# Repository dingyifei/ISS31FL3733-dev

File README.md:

# ISS31FL3733-dev
a 3733 dev board that might just work

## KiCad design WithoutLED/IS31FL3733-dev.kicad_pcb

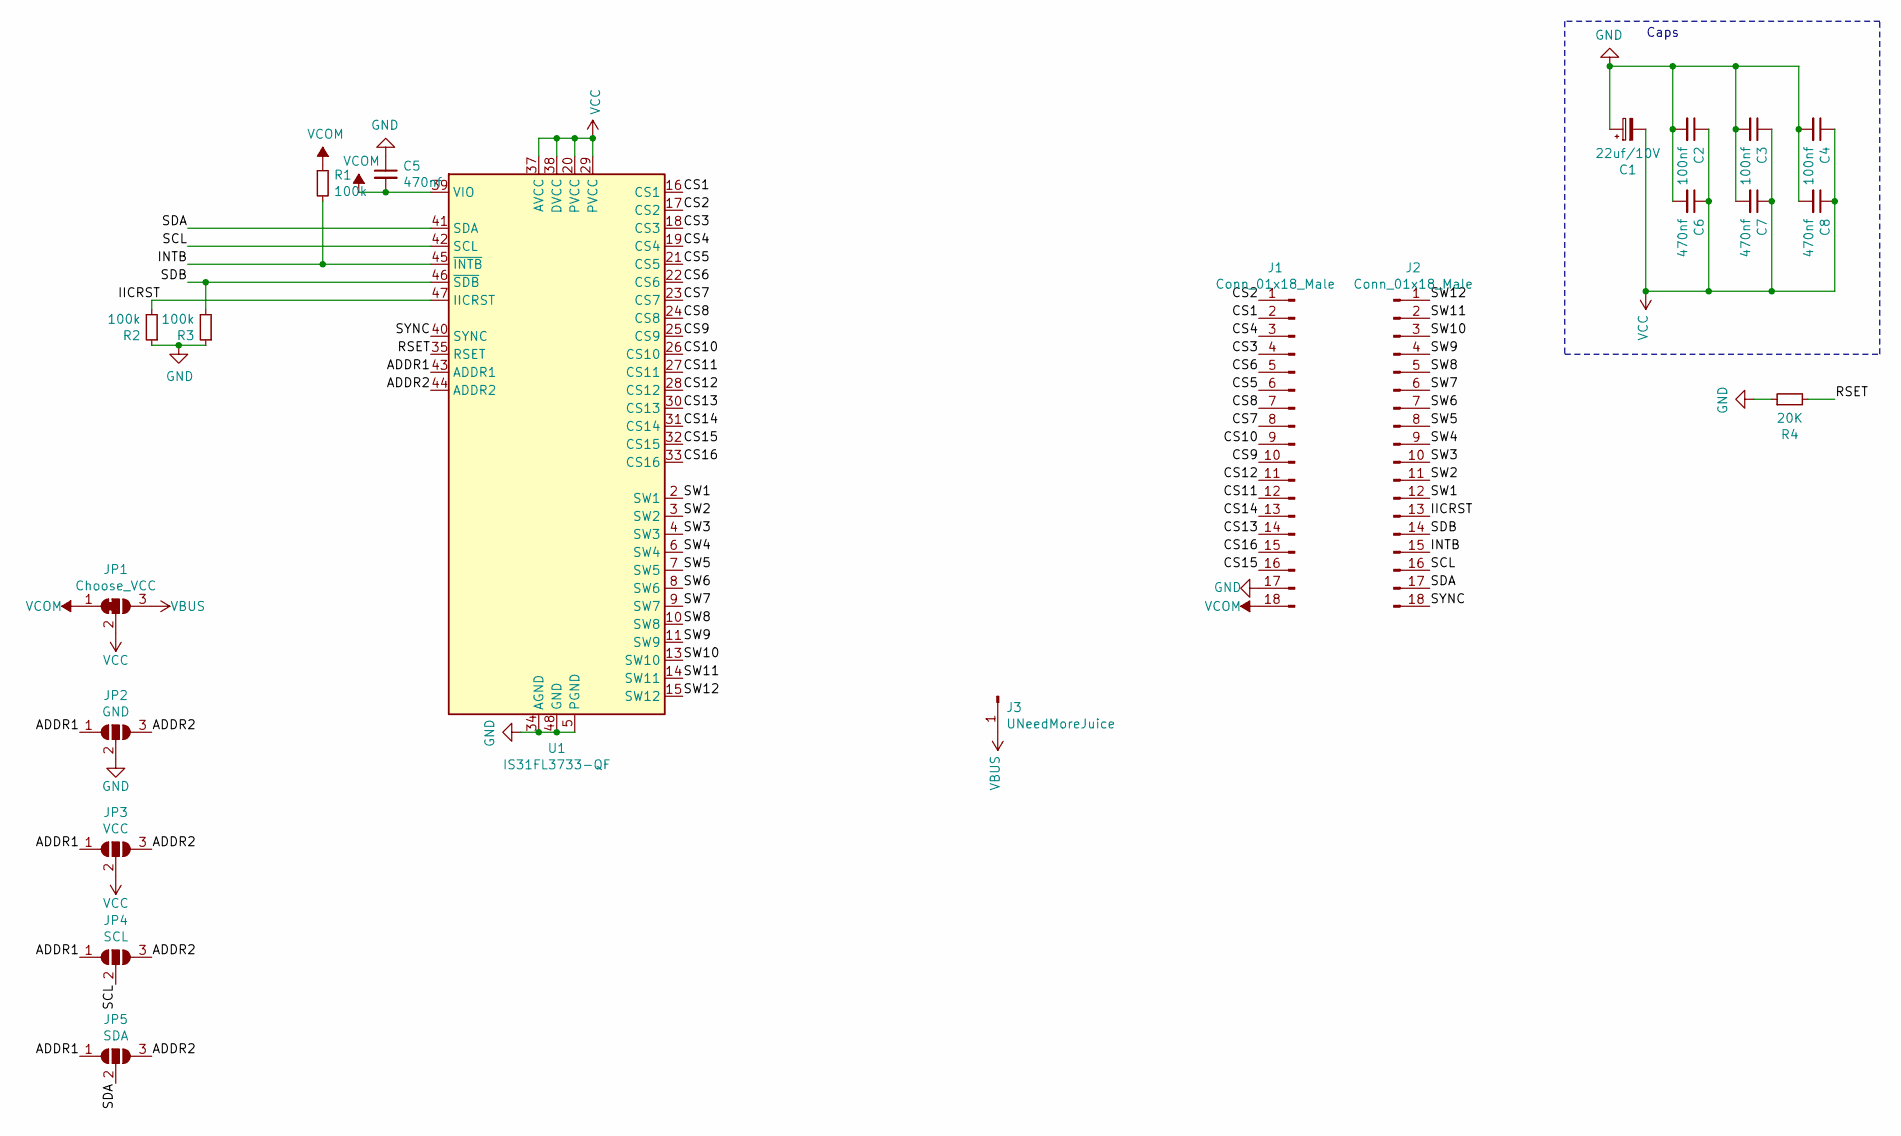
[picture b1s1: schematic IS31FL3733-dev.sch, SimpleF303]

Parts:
C1: 22uf/10V; CP_EIA-3216-18_Kemet-A; LCSC C11366
C2, C3, C4: 100nf; C_0603_1608Metric; LCSC C80516
C5, C6, C7, C8: 470nf; C_0603_1608Metric; LCSC C170149
J1, J2: Conn_01x18_Male; PinHeader_2x09_P2.00mm_Vertical
J3: UNeedMoreJuice; PinHeader_1x01_P2.00mm_Vertical
JP1: Choose_VCC; SolderJumper-3_P1.3mm_Open_RoundedPad1.0x1.5mm
JP2: GND; SolderJumper-3_P1.3mm_Open_RoundedPad1.0x1.5mm
JP3: VCC; SolderJumper-3_P1.3mm_Open_RoundedPad1.0x1.5mm
JP4: SCL; SolderJumper-3_P1.3mm_Open_RoundedPad1.0x1.5mm
JP5: SDA; SolderJumper-3_P1.3mm_Open_RoundedPad1.0x1.5mm
R1, R2, R3: 100k; R_0603_1608Metric; LCSC C100703
R4: 20K; R_0603_1608Metric; LCSC C100865
U1: IS31FL3733-QF; QFN-48-1EP_6x6mm_P0.4mm_EP4.2x4.2mm_ThermalVias

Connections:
/ADDR1: JP2.1 (A), JP3.1 (A), JP4.1 (A), JP5.1 (A), U1.43 (ADDR1)
/ADDR2: JP2.3 (B), JP3.3 (B), JP4.3 (B), JP5.3 (B), U1.44 (ADDR2)
/CS1: J1.2, U1.16 (CS1)
/CS2: J1.1, U1.17 (CS2)
/CS3: J1.4, U1.18 (CS3)
/CS4: J1.3, U1.19 (CS4)
/CS5: J1.6, U1.21 (CS5)
/CS6: J1.5, U1.22 (CS6)
/CS7: J1.8, U1.23 (CS7)
/CS8: J1.7, U1.24 (CS8)
/CS9: J1.10, U1.25 (CS9)
/CS10: J1.9, U1.26 (CS10)
/CS11: J1.12, U1.27 (CS11)
/CS12: J1.11, U1.28 (CS12)
/CS13: J1.14, U1.30 (CS13)
/CS14: J1.13, U1.31 (CS14)
/CS15: J1.16, U1.32 (CS15)
/CS16: J1.15, U1.33 (CS16)
/IICRST: J2.13, R2.2, U1.47 (IICRST)
/INTB: J2.15, R1.2, U1.45 (~INTB)
/RSET: R4.2, U1.35 (RSET)
/SCL: J2.16, JP4.2 (C), U1.42 (SCL)
/SDA: J2.17, JP5.2 (C), U1.41 (SDA)
/SDB: J2.14, R3.2, U1.46 (~SDB)
/SW1: J2.12, U1.2 (SW1)
/SW2: J2.11, U1.3 (SW2)
/SW3: J2.10, U1.4 (SW3)
/SW4: J2.9, U1.6 (SW4)
/SW5: J2.8, U1.7 (SW5)
/SW6: J2.7, U1.8 (SW6)
/SW7: J2.6, U1.9 (SW7)
/SW8: J2.5, U1.10 (SW8)
/SW9: J2.4, U1.11 (SW9)
/SW10: J2.3, U1.13 (SW10)
/SW11: J2.2, U1.14 (SW11)
/SW12: J2.1, U1.15 (SW12)
/SYNC: J2.18, U1.40 (SYNC)
GND: C1.1, C2.2, C3.2, C4.2, C5.1, C6.2, C7.2, C8.2, J1.17, JP2.2 (C), R2.1, R3.1, R4.1, U1.5 (PGND), U1.12 (PGND), U1.34 (AGND), U1.48 (GND), U1.49 (GND)
VBUS: J3.1, JP1.3 (B)
VCC: C1.2, C2.1, C3.1, C4.1, C6.1, C7.1, C8.1, JP1.2 (C), JP3.2 (C), U1.20 (PVCC), U1.29 (PVCC), U1.37 (AVCC), U1.38 (DVCC)
VCOM: C5.2, J1.18, JP1.1 (A), R1.1, U1.39 (VIO)

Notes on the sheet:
Caps

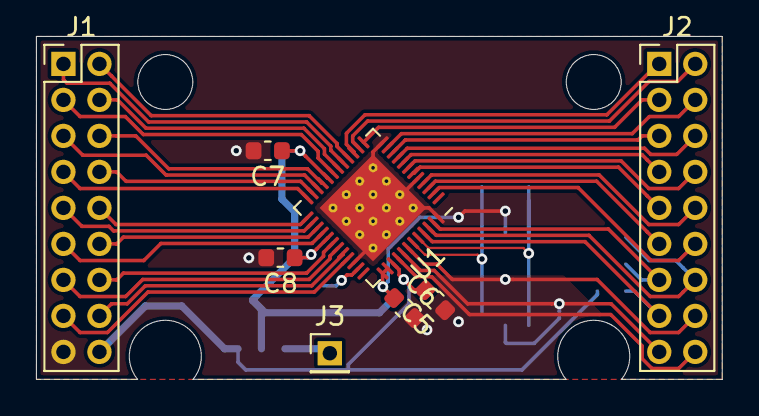
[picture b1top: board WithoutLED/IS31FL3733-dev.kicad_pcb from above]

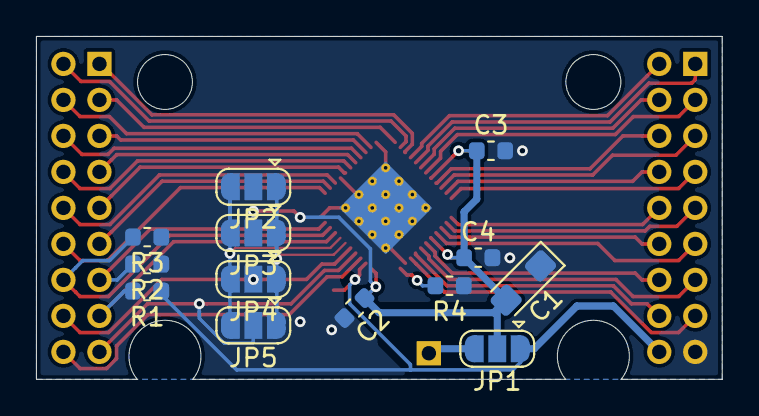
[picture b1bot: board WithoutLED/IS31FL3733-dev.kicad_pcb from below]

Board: 2 copper layers, 38.1 x 19.1 mm, 21 parts (13 on the bottom side), 41 nets.

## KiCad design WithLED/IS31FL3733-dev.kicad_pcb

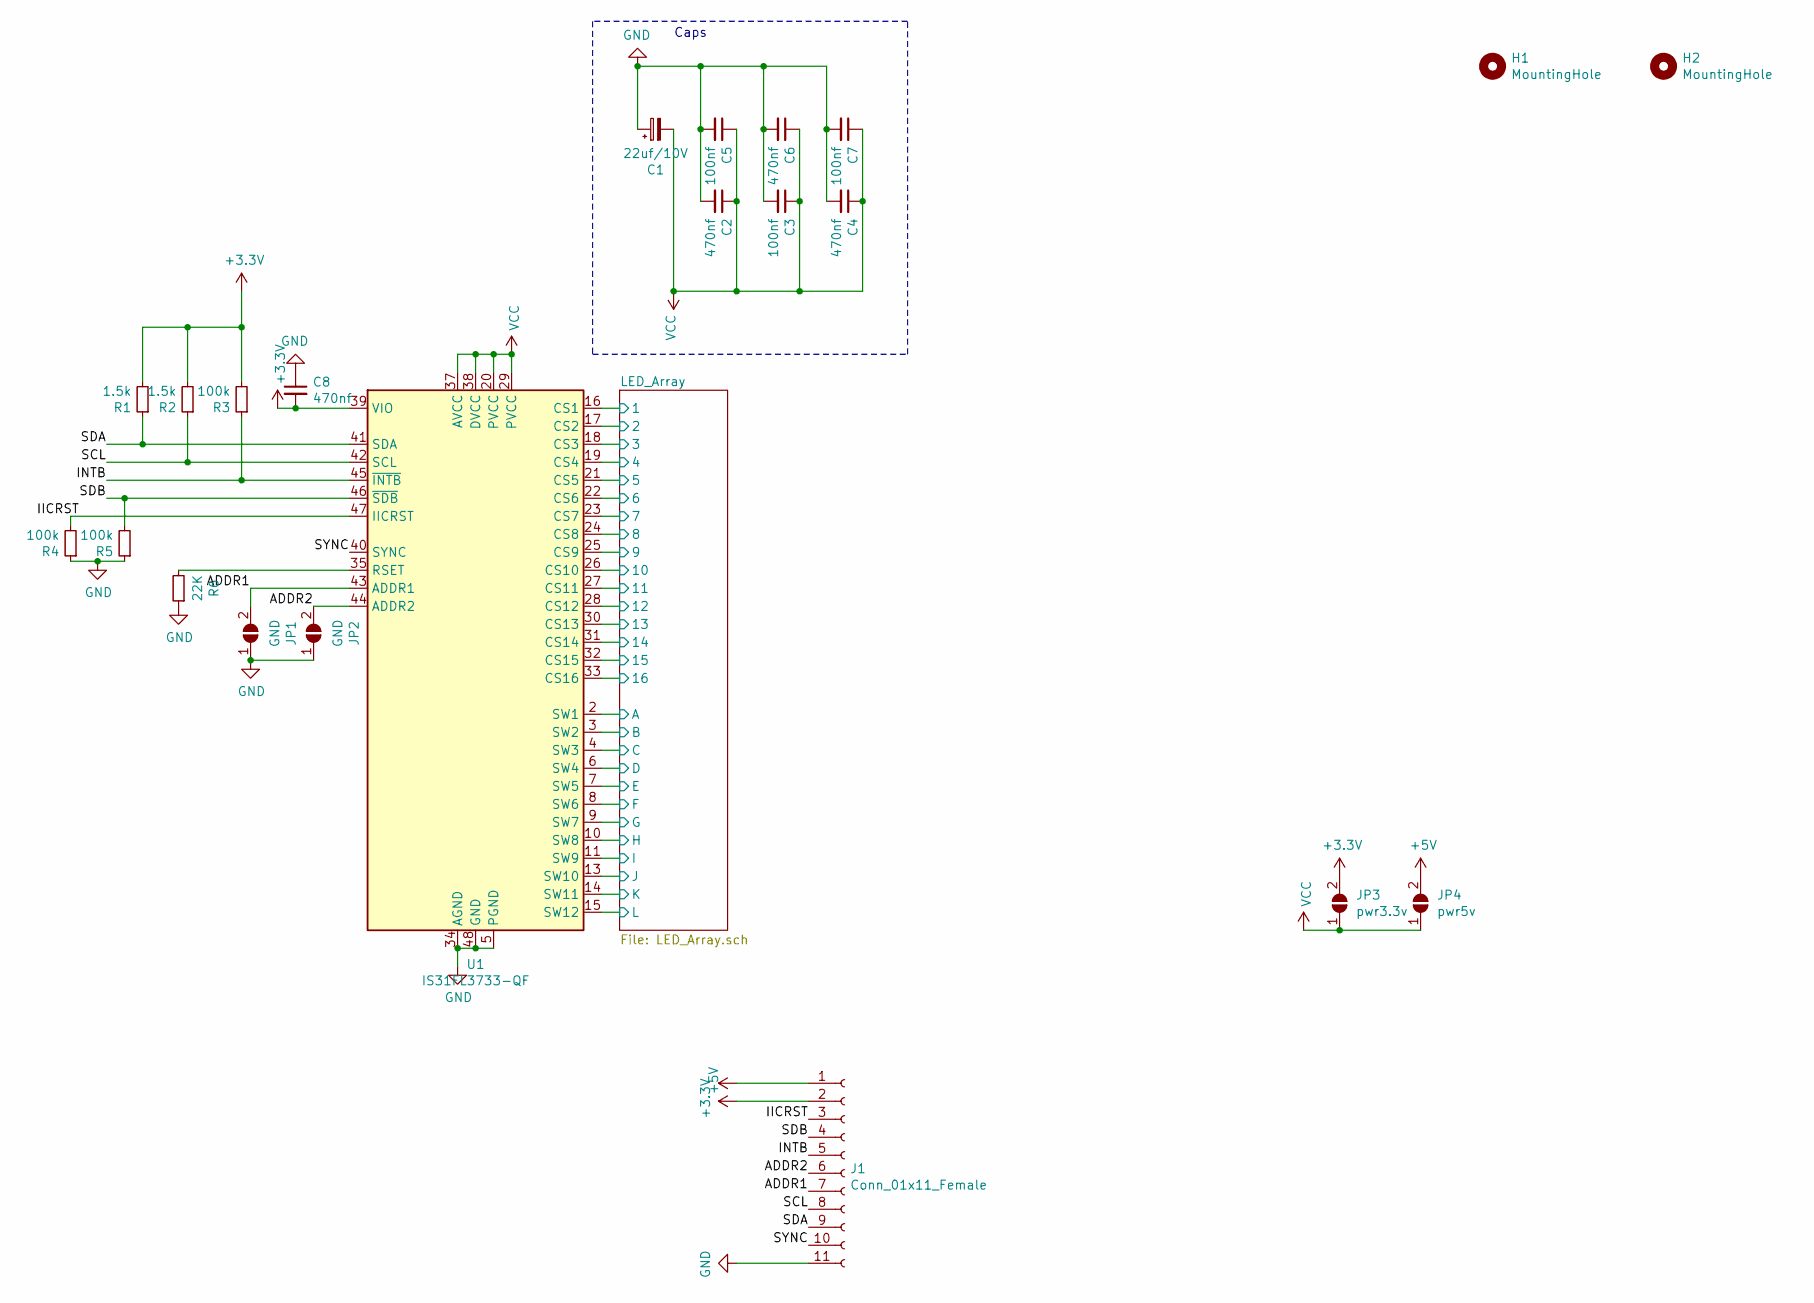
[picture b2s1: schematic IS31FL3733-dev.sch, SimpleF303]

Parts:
C1: 22uf/10V; CP_EIA-3216-18_Kemet-A; LCSC C11366
C2, C4, C6, C8: 470nf; C_0603_1608Metric; LCSC C170149
C3, C5, C7: 100nf; C_0603_1608Metric; LCSC C80516
H1, H2: MountingHole; MountingHole_2.1mm; LCSC C2337
J1: Conn_01x11_Female; PinSocket_1x11_P2.54mm_Vertical; LCSC C2337
JP1, JP2: GND; SolderJumper-2_P1.3mm_Open_TrianglePad1.0x1.5mm
JP3: pwr3.3v; SolderJumper-2_P1.3mm_Open_TrianglePad1.0x1.5mm
JP4: pwr5v; SolderJumper-2_P1.3mm_Open_TrianglePad1.0x1.5mm
R1, R2: 1.5k; R_0603_1608Metric; LCSC C103303
R3, R4, R5: 100k; R_0603_1608Metric; LCSC C100703
R6: 22K; R_0603_1608Metric; LCSC C100865
U1: IS31FL3733-QF; QFN-48-1EP_6x6mm_P0.4mm_EP4.2x4.2mm_ThermalVias

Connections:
+3V3: C8.2, J1.2, JP3.2 (B), R1.2, R2.2, R3.2, U1.39 (VIO)
+5V: J1.1, JP4.2 (B)
/ADDR1: J1.7, JP1.2 (B), U1.43 (ADDR1)
/ADDR2: J1.6, JP2.2 (B), U1.44 (ADDR2)
/IICRST: J1.3, R4.2, U1.47 (IICRST)
/INTB: J1.5, R3.1, U1.45 (~INTB)
/LED_Array/1: U1.16 (CS1); also elsewhere on the board
/LED_Array/2: U1.17 (CS2); also elsewhere on the board
/LED_Array/3: U1.18 (CS3); also elsewhere on the board
/LED_Array/4: U1.19 (CS4); also elsewhere on the board
/LED_Array/5: U1.21 (CS5); also elsewhere on the board
/LED_Array/6: U1.22 (CS6); also elsewhere on the board
/LED_Array/7: U1.23 (CS7); also elsewhere on the board
/LED_Array/8: U1.24 (CS8); also elsewhere on the board
/LED_Array/9: U1.25 (CS9); also elsewhere on the board
/LED_Array/10: U1.26 (CS10); also elsewhere on the board
/LED_Array/11: U1.27 (CS11); also elsewhere on the board
/LED_Array/12: U1.28 (CS12); also elsewhere on the board
/LED_Array/13: U1.30 (CS13); also elsewhere on the board
/LED_Array/14: U1.31 (CS14); also elsewhere on the board
/LED_Array/15: U1.32 (CS15); also elsewhere on the board
/LED_Array/16: U1.33 (CS16); also elsewhere on the board
/LED_Array/A: U1.2 (SW1); also elsewhere on the board
/LED_Array/B: U1.3 (SW2); also elsewhere on the board
/LED_Array/C: U1.4 (SW3); also elsewhere on the board
/LED_Array/D: U1.6 (SW4); also elsewhere on the board
/LED_Array/E: U1.7 (SW5); also elsewhere on the board
/LED_Array/F: U1.8 (SW6); also elsewhere on the board
/LED_Array/G: U1.9 (SW7); also elsewhere on the board
/LED_Array/H: U1.10 (SW8); also elsewhere on the board
/LED_Array/I: U1.11 (SW9); also elsewhere on the board
/LED_Array/J: U1.13 (SW10); also elsewhere on the board
/LED_Array/K: U1.14 (SW11); also elsewhere on the board
/LED_Array/L: U1.15 (SW12); also elsewhere on the board
/SCL: J1.8, R2.1, U1.42 (SCL)
/SDA: J1.9, R1.1, U1.41 (SDA)
/SDB: J1.4, R5.2, U1.46 (~SDB)
/SYNC: J1.10, U1.40 (SYNC)
GND: C1.1, C2.2, C3.2, C4.2, C5.2, C6.2, C7.2, C8.1, J1.11, JP1.1 (A), JP2.1 (A), R4.1, R5.1, R6.1, U1.5 (PGND), U1.12 (PGND), U1.34 (AGND), U1.48 (GND), U1.49 (GND)
unnamed: R6.2, U1.35 (RSET)
VCC: C1.2, C2.1, C3.1, C4.1, C5.1, C6.1, C7.1, JP3.1 (A), JP4.1 (A), U1.20 (PVCC), U1.29 (PVCC), U1.37 (AVCC), U1.38 (DVCC)

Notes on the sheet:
Caps

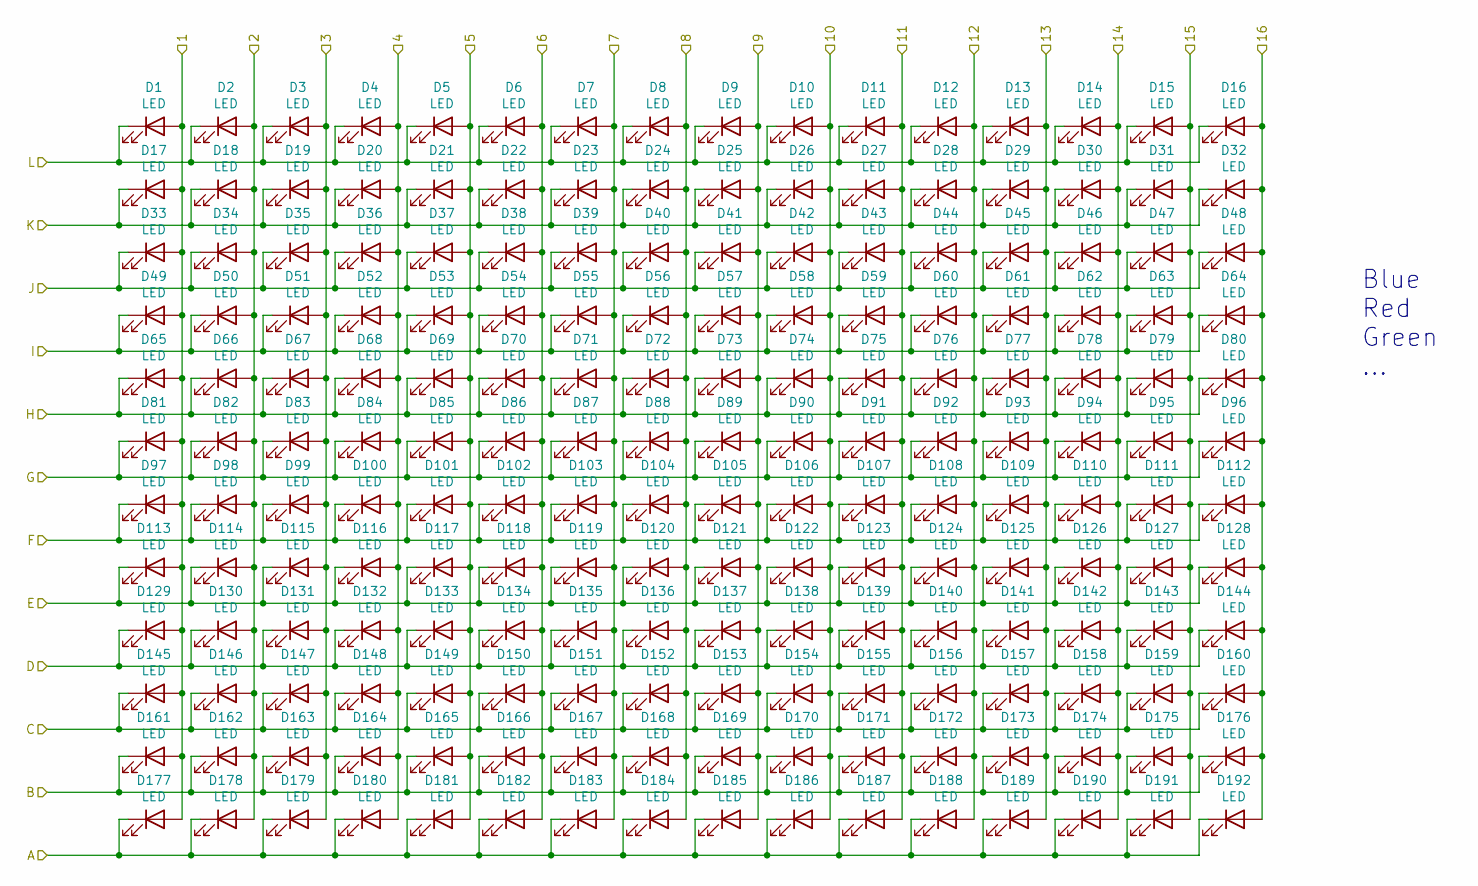
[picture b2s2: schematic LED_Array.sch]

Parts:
D1, D2, D3, D4, D5, D6, D7, D8, D9, D10, D11, D12, D13, D14, D15, D16, D17, D18, D19, D20, D21, D22, D23, D24, D25, D26, D27, D28, D29, D30, D31, D32, D33, D34, D35, D36, D37, D38, D39, D40, D41, D42, D43, D44, D45, D46, D47, D48, D49, D50, D51, D52, D53, D54, D55, D56, D57, D58, D59, D60, D61, D62, D63, D64, D65, D66, D67, D68, D69, D70, D71, D72, D73, D74, D75, D76, D77, D78, D79, D80, D81, D82, D83, D84, D85, D86, D87, D88, D89, D90, D91, D92, D93, D94, D95, D96, D97, D98, D99, D100, D101, D102, D103, D104, D105, D106, D107, D108, D109, D110, D111, D112, D113, D114, D115, D116, D117, D118, D119, D120, D121, D122, D123, D124, D125, D126, D127, D128, D129, D130, D131, D132, D133, D134, D135, D136, D137, D138, D139, D140, D141, D142, D143, D144, D145, D146, D147, D148, D149, D150, D151, D152, D153, D154, D155, D156, D157, D158, D159, D160, D161, D162, D163, D164, D165, D166, D167, D168, D169, D170, D171, D172, D173, D174, D175, D176, D177, D178, D179, D180, D181, D182, D183, D184, D185, D186, D187, D188, D189, D190, D191, D192: LED; LED_0603_1608Metric_HideText

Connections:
/LED_Array/1: D1.2 (A), D17.2 (A), D33.2 (A), D49.2 (A), D65.2 (A), D81.2 (A), D97.2 (A), D113.2 (A), D129.2 (A), D145.2 (A), D161.2 (A), D177.2 (A); also elsewhere on the board
/LED_Array/2: D2.2 (A), D18.2 (A), D34.2 (A), D50.2 (A), D66.2 (A), D82.2 (A), D98.2 (A), D114.2 (A), D130.2 (A), D146.2 (A), D162.2 (A), D178.2 (A); also elsewhere on the board
/LED_Array/3: D3.2 (A), D19.2 (A), D35.2 (A), D51.2 (A), D67.2 (A), D83.2 (A), D99.2 (A), D115.2 (A), D131.2 (A), D147.2 (A), D163.2 (A), D179.2 (A); also elsewhere on the board
/LED_Array/4: D4.2 (A), D20.2 (A), D36.2 (A), D52.2 (A), D68.2 (A), D84.2 (A), D100.2 (A), D116.2 (A), D132.2 (A), D148.2 (A), D164.2 (A), D180.2 (A); also elsewhere on the board
/LED_Array/5: D5.2 (A), D21.2 (A), D37.2 (A), D53.2 (A), D69.2 (A), D85.2 (A), D101.2 (A), D117.2 (A), D133.2 (A), D149.2 (A), D165.2 (A), D181.2 (A); also elsewhere on the board
/LED_Array/6: D6.2 (A), D22.2 (A), D38.2 (A), D54.2 (A), D70.2 (A), D86.2 (A), D102.2 (A), D118.2 (A), D134.2 (A), D150.2 (A), D166.2 (A), D182.2 (A); also elsewhere on the board
/LED_Array/7: D7.2 (A), D23.2 (A), D39.2 (A), D55.2 (A), D71.2 (A), D87.2 (A), D103.2 (A), D119.2 (A), D135.2 (A), D151.2 (A), D167.2 (A), D183.2 (A); also elsewhere on the board
/LED_Array/8: D8.2 (A), D24.2 (A), D40.2 (A), D56.2 (A), D72.2 (A), D88.2 (A), D104.2 (A), D120.2 (A), D136.2 (A), D152.2 (A), D168.2 (A), D184.2 (A); also elsewhere on the board
/LED_Array/9: D9.2 (A), D25.2 (A), D41.2 (A), D57.2 (A), D73.2 (A), D89.2 (A), D105.2 (A), D121.2 (A), D137.2 (A), D153.2 (A), D169.2 (A), D185.2 (A); also elsewhere on the board
/LED_Array/10: D10.2 (A), D26.2 (A), D42.2 (A), D58.2 (A), D74.2 (A), D90.2 (A), D106.2 (A), D122.2 (A), D138.2 (A), D154.2 (A), D170.2 (A), D186.2 (A); also elsewhere on the board
/LED_Array/11: D11.2 (A), D27.2 (A), D43.2 (A), D59.2 (A), D75.2 (A), D91.2 (A), D107.2 (A), D123.2 (A), D139.2 (A), D155.2 (A), D171.2 (A), D187.2 (A); also elsewhere on the board
/LED_Array/12: D12.2 (A), D28.2 (A), D44.2 (A), D60.2 (A), D76.2 (A), D92.2 (A), D108.2 (A), D124.2 (A), D140.2 (A), D156.2 (A), D172.2 (A), D188.2 (A); also elsewhere on the board
/LED_Array/13: D13.2 (A), D29.2 (A), D45.2 (A), D61.2 (A), D77.2 (A), D93.2 (A), D109.2 (A), D125.2 (A), D141.2 (A), D157.2 (A), D173.2 (A), D189.2 (A); also elsewhere on the board
/LED_Array/14: D14.2 (A), D30.2 (A), D46.2 (A), D62.2 (A), D78.2 (A), D94.2 (A), D110.2 (A), D126.2 (A), D142.2 (A), D158.2 (A), D174.2 (A), D190.2 (A); also elsewhere on the board
/LED_Array/15: D15.2 (A), D31.2 (A), D47.2 (A), D63.2 (A), D79.2 (A), D95.2 (A), D111.2 (A), D127.2 (A), D143.2 (A), D159.2 (A), D175.2 (A), D191.2 (A); also elsewhere on the board
/LED_Array/16: D16.2 (A), D32.2 (A), D48.2 (A), D64.2 (A), D80.2 (A), D96.2 (A), D112.2 (A), D128.2 (A), D144.2 (A), D160.2 (A), D176.2 (A), D192.2 (A); also elsewhere on the board
/LED_Array/A: D177.1 (K), D178.1 (K), D179.1 (K), D180.1 (K), D181.1 (K), D182.1 (K), D183.1 (K), D184.1 (K), D185.1 (K), D186.1 (K), D187.1 (K), D188.1 (K), D189.1 (K), D190.1 (K), D191.1 (K), D192.1 (K); also elsewhere on the board
/LED_Array/B: D161.1 (K), D162.1 (K), D163.1 (K), D164.1 (K), D165.1 (K), D166.1 (K), D167.1 (K), D168.1 (K), D169.1 (K), D170.1 (K), D171.1 (K), D172.1 (K), D173.1 (K), D174.1 (K), D175.1 (K), D176.1 (K); also elsewhere on the board
/LED_Array/C: D145.1 (K), D146.1 (K), D147.1 (K), D148.1 (K), D149.1 (K), D150.1 (K), D151.1 (K), D152.1 (K), D153.1 (K), D154.1 (K), D155.1 (K), D156.1 (K), D157.1 (K), D158.1 (K), D159.1 (K), D160.1 (K); also elsewhere on the board
/LED_Array/D: D129.1 (K), D130.1 (K), D131.1 (K), D132.1 (K), D133.1 (K), D134.1 (K), D135.1 (K), D136.1 (K), D137.1 (K), D138.1 (K), D139.1 (K), D140.1 (K), D141.1 (K), D142.1 (K), D143.1 (K), D144.1 (K); also elsewhere on the board
/LED_Array/E: D113.1 (K), D114.1 (K), D115.1 (K), D116.1 (K), D117.1 (K), D118.1 (K), D119.1 (K), D120.1 (K), D121.1 (K), D122.1 (K), D123.1 (K), D124.1 (K), D125.1 (K), D126.1 (K), D127.1 (K), D128.1 (K); also elsewhere on the board
/LED_Array/F: D97.1 (K), D98.1 (K), D99.1 (K), D100.1 (K), D101.1 (K), D102.1 (K), D103.1 (K), D104.1 (K), D105.1 (K), D106.1 (K), D107.1 (K), D108.1 (K), D109.1 (K), D110.1 (K), D111.1 (K), D112.1 (K); also elsewhere on the board
/LED_Array/G: D81.1 (K), D82.1 (K), D83.1 (K), D84.1 (K), D85.1 (K), D86.1 (K), D87.1 (K), D88.1 (K), D89.1 (K), D90.1 (K), D91.1 (K), D92.1 (K), D93.1 (K), D94.1 (K), D95.1 (K), D96.1 (K); also elsewhere on the board
/LED_Array/H: D65.1 (K), D66.1 (K), D67.1 (K), D68.1 (K), D69.1 (K), D70.1 (K), D71.1 (K), D72.1 (K), D73.1 (K), D74.1 (K), D75.1 (K), D76.1 (K), D77.1 (K), D78.1 (K), D79.1 (K), D80.1 (K); also elsewhere on the board
/LED_Array/I: D49.1 (K), D50.1 (K), D51.1 (K), D52.1 (K), D53.1 (K), D54.1 (K), D55.1 (K), D56.1 (K), D57.1 (K), D58.1 (K), D59.1 (K), D60.1 (K), D61.1 (K), D62.1 (K), D63.1 (K), D64.1 (K); also elsewhere on the board
/LED_Array/J: D33.1 (K), D34.1 (K), D35.1 (K), D36.1 (K), D37.1 (K), D38.1 (K), D39.1 (K), D40.1 (K), D41.1 (K), D42.1 (K), D43.1 (K), D44.1 (K), D45.1 (K), D46.1 (K), D47.1 (K), D48.1 (K); also elsewhere on the board
/LED_Array/K: D17.1 (K), D18.1 (K), D19.1 (K), D20.1 (K), D21.1 (K), D22.1 (K), D23.1 (K), D24.1 (K), D25.1 (K), D26.1 (K), D27.1 (K), D28.1 (K), D29.1 (K), D30.1 (K), D31.1 (K), D32.1 (K); also elsewhere on the board
/LED_Array/L: D1.1 (K), D2.1 (K), D3.1 (K), D4.1 (K), D5.1 (K), D6.1 (K), D7.1 (K), D8.1 (K), D9.1 (K), D10.1 (K), D11.1 (K), D12.1 (K), D13.1 (K), D14.1 (K), D15.1 (K), D16.1 (K); also elsewhere on the board

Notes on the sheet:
Blue Red Green ...

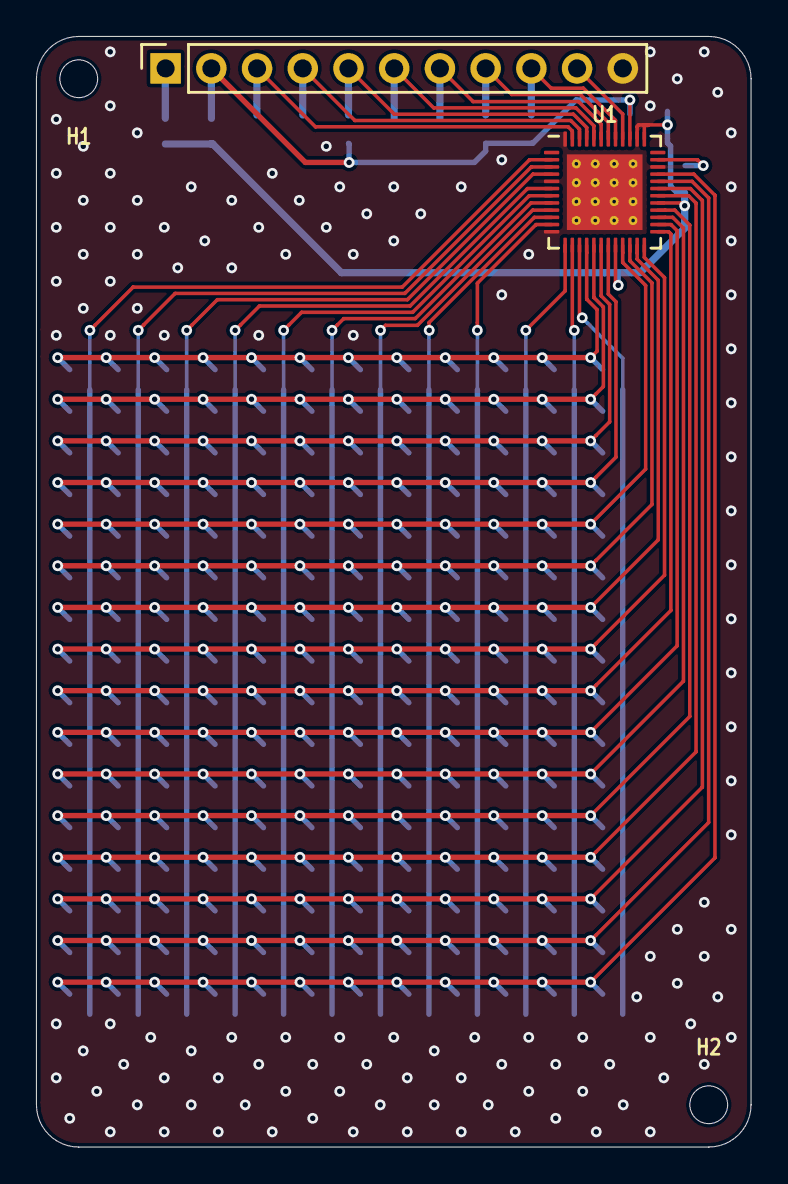
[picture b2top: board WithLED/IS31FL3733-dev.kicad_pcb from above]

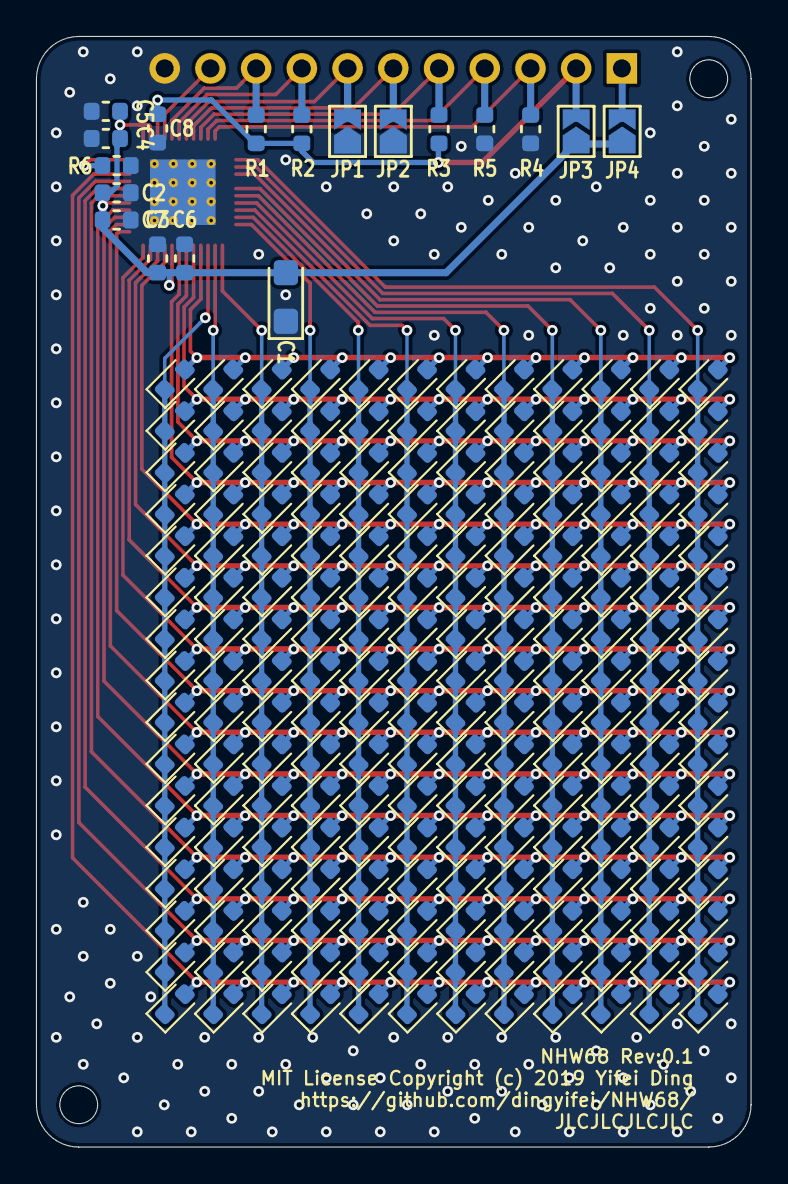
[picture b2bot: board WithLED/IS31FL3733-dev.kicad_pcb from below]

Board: 2 copper layers, 39.7 x 61.7 mm, 214 parts (210 on the bottom side), 41 nets.

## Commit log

2020-02-15 It use reverse mount, I will consider changing it
2020-02-16 monocolor? or it could actually go multicolor?
2020-02-16 fix license
2020-02-17 It should work just fine
2020-02-20 im dumb today
2020-02-21 Appearently buy parts is hard
2020-03-30 fix problems with the board
2020-04-05 I have a great idea.....
2020-04-16 I think it can turn on

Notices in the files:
WithLED/IS31FL3733-dev.kicad_pcb:
MIT License Copyright (c) 2019 Yifei Ding
